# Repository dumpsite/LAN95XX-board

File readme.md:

SMSC LAN95XX adapter board
==========================

This board serves as a carrier for the famous LAN95XX 
(LAN9512, LAN9513 or LAN9514) USB to fast Ethernet controller.

All the (high) frequency-, power- and decoupling stuff is done
on the board, while the most interesting pins are routed to the
outside edges. There the pitch is the usual 2.54mm (0.1") and
easily accessible for any further projects.

The board features an onboard eeprom (type "93C56 or 93C66") in cheap
SO8 package and implements a 25 MHz 5032 SMD crystal circuit.
(For cheaper HC49* versions there was no space...)
The smallest component is 0603, but most of them are replaceable with some 0805...

All is done (and works!) with two active design layers only!
A theoretical third layer is "emulated" by connecting some edge-pins together.
So it needs not be produced with the PCB itself...
The traces are scaled a bit thinner to compensate spreading during design transfer
to copper. All package footprints are using longer pin pads.
The primary IC (LAN95XX) QFN package footprint is extended by an 3.2mm inner
bonding hole, allowing backside soldering and solder bridging the two layers.

All this allows fully DIY capability and "etching at home".
VIAs can be drilled using 0.2mm or 0.3mm drill.
Side-to-side bonding can be done using stripped AWG30 wire wrapping wire.

The minimal essential size is "33mm x 33mm" using castellations or
"36mm x 36mm" using full pin headers.
Including the whole PCB area having the board nicely centered, its
dimensions are "50mm x 50mm" .

All the content is open and freely usable in non commercial applications.
It would be very kind to mention me in your projects and ask me first if you plan commercial use...

by Stephan Baerwolf (stephan@matrixstorm.com), Schwansee 2016

(who is not bearing any responsibility or guarantee of any kind for his projects)

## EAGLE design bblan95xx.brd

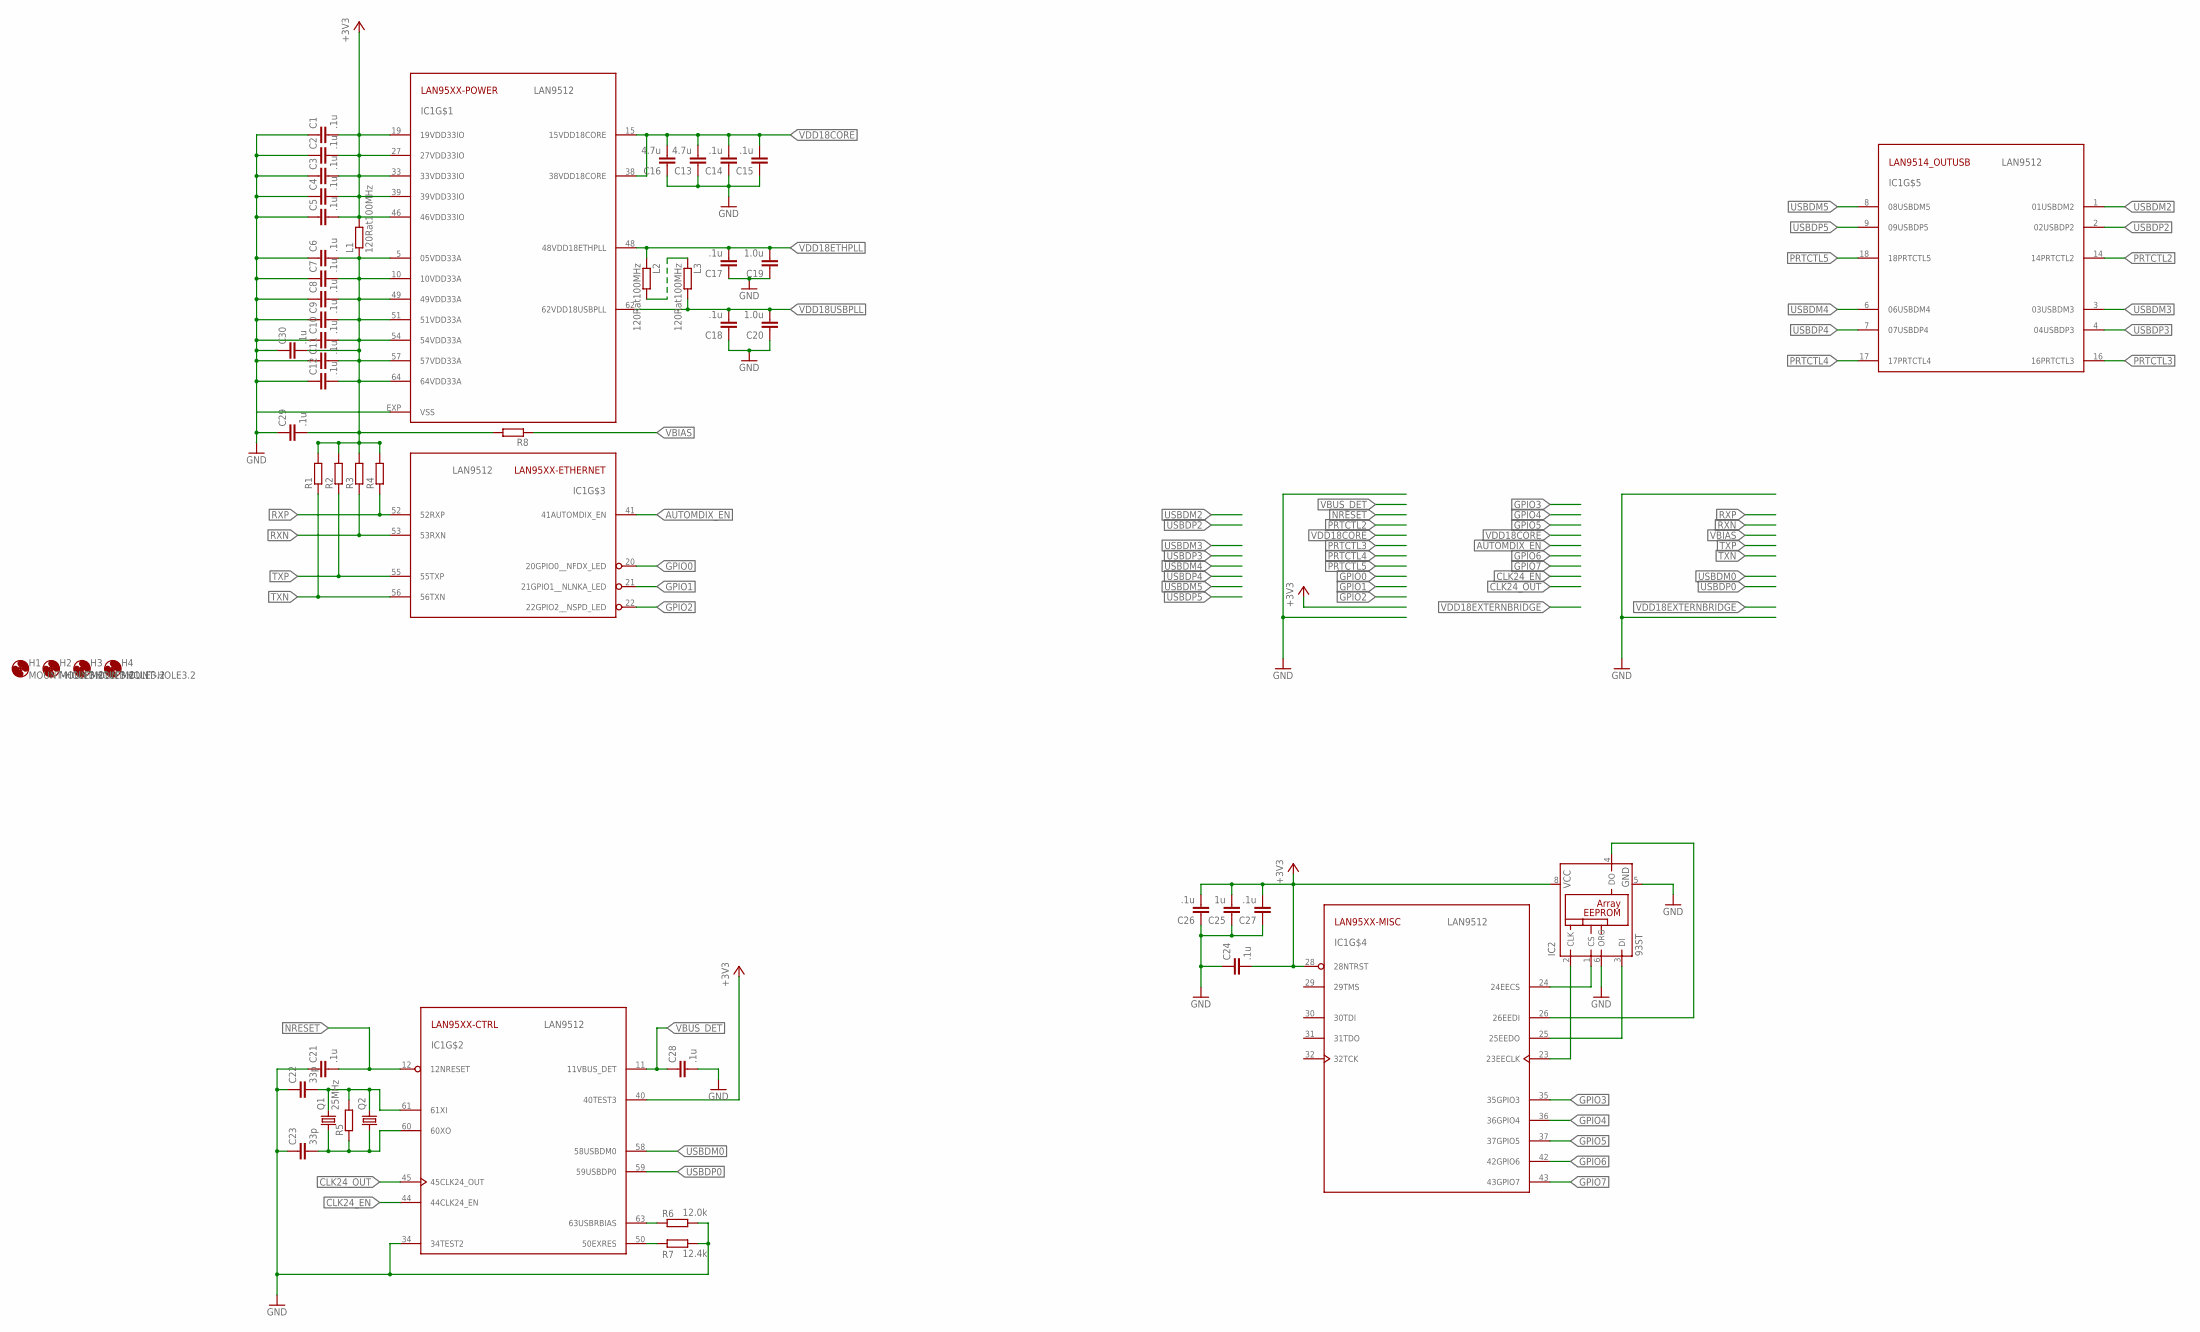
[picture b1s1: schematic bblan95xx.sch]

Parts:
C1, C2, C3, C4, C5, C6, C7, C8, C12, C26, C27: .1u; C0805K
C9, C10, C11, C14, C15, C17, C18, C21, C24, C28, C29, C30: .1u; C0603K
C13, C16: 4.7u; C0805K
C19, C20: 1.0u; C0805K
C22, C23: 33p; C0603K
C25: 1u; C0805K
H1, H2, H3, H4: MOUNT-HOLE3.2; 3,2
IC1: LAN9512; QFN64-9X9-EXTRALONG
IC2: 93ST; SO-08
L1, L2, L3: 120Rat100MHz; R0805
Q1: 25MHz; CRYSTAL-SMD-5X3
Q2: CRYSTALHC49S; HC49/S
R1, R2, R3, R4, R5: R-EU_R0603; R0603
R6: 12.0k; R0603
R7: 12.4k; R0603
R8: R-EU_R0402; R0402

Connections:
+3V3: C1.2, C2.2, C3.2, C4.2, C5.2, C24.2, C25.2, C26.2, C27.2, IC1.19 (19VDD33IO), IC1.27 (27VDD33IO), IC1.28 (28NTRST), IC1.33 (33VDD33IO), IC1.39 (39VDD33IO), IC1.40 (40TEST3), IC1.46 (46VDD33IO), IC2.8 (VCC), L1.2
AUTOMDIX_EN: IC1.41 (41AUTOMDIX_EN)
CLK24_EN: IC1.44 (44CLK24_EN)
CLK24_OUT: IC1.45 (45CLK24_OUT)
EECLK: IC1.23 (23EECLK), IC2.2 (CLK)
EECS: IC1.24 (24EECS), IC2.1 (CS)
EEDI: IC1.26 (26EEDI), IC2.4 (DO)
EEDO: IC1.25 (25EEDO), IC2.3 (DI)
GND: C1.1, C2.1, C3.1, C4.1, C5.1, C6.1, C7.1, C8.1, C9.1, C10.1, C11.1, C12.1, C13.1, C14.1, C15.1, C16.1, C17.1, C18.1, C19.1, C20.1, C21.1, C22.1, C23.1, C24.1, C25.1, C26.1, C27.1, C28.2, C29.1, C30.1, IC1.34 (34TEST2), IC1.EXP (VSS), IC2.5 (GND), IC2.6 (ORG), R6.2, R7.2
GPIO0: IC1.20 (20GPIO0__NFDX_LED)
GPIO1: IC1.21 (21GPIO1__NLNKA_LED)
GPIO2: IC1.22 (22GPIO2__NSPD_LED)
GPIO3: IC1.35 (35GPIO3)
GPIO4: IC1.36 (36GPIO4)
GPIO5: IC1.37 (37GPIO5)
GPIO6: IC1.42 (42GPIO6)
GPIO7: IC1.43 (43GPIO7)
unnamed: IC1.63 (63USBRBIAS), R6.1
unnamed: IC1.50 (50EXRES), R7.1
NRESET: C21.2, IC1.12 (12NRESET)
PRTCTL2: IC1.14 (14PRTCTL2)
PRTCTL3: IC1.16 (16PRTCTL3)
PRTCTL4: IC1.17 (17PRTCTL4)
PRTCTL5: IC1.18 (18PRTCTL5)
RXN: IC1.53 (53RXN), R3.1
RXP: IC1.52 (52RXP), R4.1
TXN: IC1.56 (56TXN), R1.1
TXP: IC1.55 (55TXP), R2.1
USBDM0: IC1.58 (58USBDM0)
USBDM2: IC1.1 (01USBDM2)
USBDM3: IC1.3 (03USBDM3)
USBDM4: IC1.6 (06USBDM4)
USBDM5: IC1.8 (08USBDM5)
USBDP0: IC1.59 (59USBDP0)
USBDP2: IC1.2 (02USBDP2)
USBDP3: IC1.4 (04USBDP3)
USBDP4: IC1.7 (07USBDP4)
USBDP5: IC1.9 (09USBDP5)
VBIAS: R8.1
VBUS_DET: C28.1, IC1.11 (11VBUS_DET)
VDD18CORE: C13.2, C14.2, C15.2, C16.2, IC1.15 (15VDD18CORE), IC1.38 (38VDD18CORE)
VDD18ETHPLL: C17.2, C19.2, IC1.48 (48VDD18ETHPLL), L2.1
VDD18EXTERNBRIDGE: L2.2, L3.1
VDD18USBPLL: C18.2, C20.2, IC1.62 (62VDD18USBPLL), L3.2
VDD33A: C6.2, C7.2, C8.2, C9.2, C10.2, C11.2, C12.2, C29.2, C30.2, IC1.5 (05VDD33A), IC1.10 (10VDD33A), IC1.49 (49VDD33A), IC1.51 (51VDD33A), IC1.54 (54VDD33A), IC1.57 (57VDD33A), IC1.64 (64VDD33A), L1.1, R1.2, R2.2, R3.2, R4.2, R8.2
XI: C22.2, IC1.61 (61XI), Q1.3 (2), Q2.2, R5.2
XO: C23.2, IC1.60 (60XO), Q1.1, Q2.1, R5.1

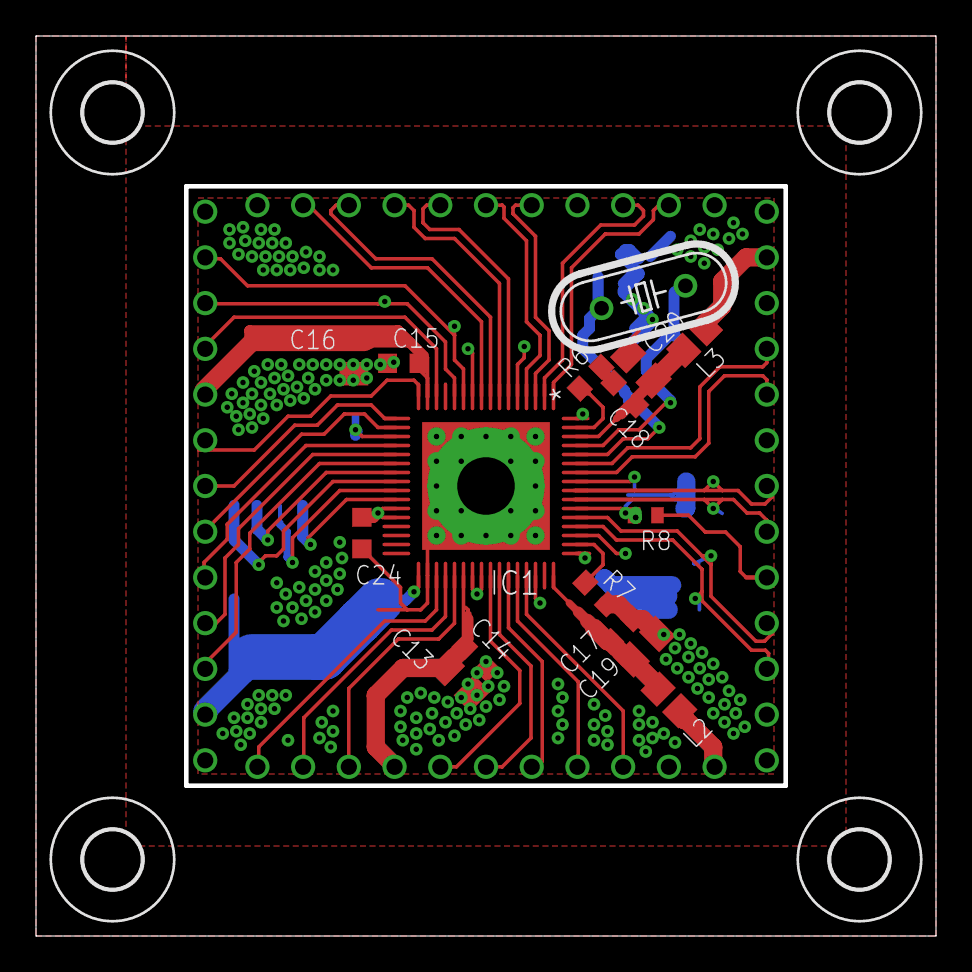
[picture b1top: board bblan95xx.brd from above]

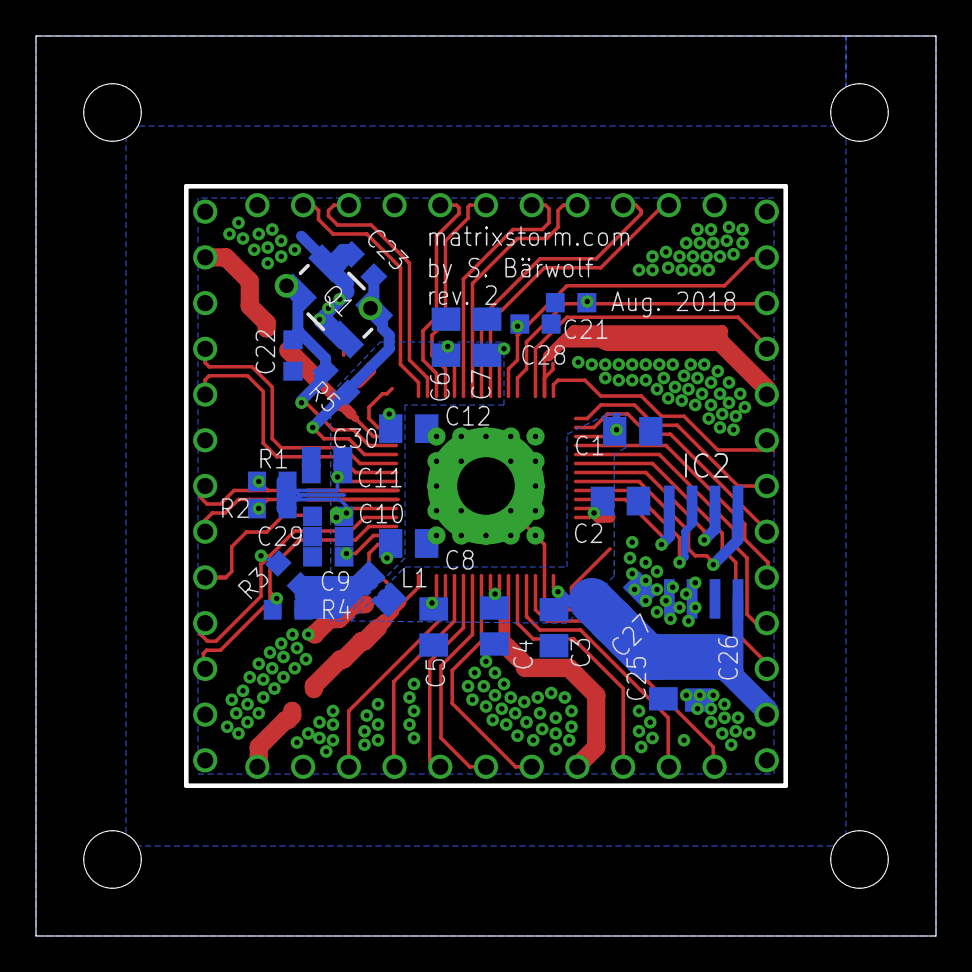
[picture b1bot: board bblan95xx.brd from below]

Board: 3 copper layers, 49.7 x 49.7 mm, 49 parts (29 on the bottom side), 21 nets.

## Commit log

2016-10-16 initial repository fill
2016-10-16 starting LAN95xx base board design
2016-10-16 shrink primary polygons to final adapter size
2016-10-16 add extra 0603 cap and make 0603 to 0805 where possible
2016-10-16 add extra analog capacitor and route VDD33A to free PIN
2016-10-16 accept all warnings and errors since board is fine
2016-10-16 add more vias to connect GND planes
2016-10-16 add also thermal vias to main IC
2016-10-16 mirror pinjumper headers in bottom direction
2016-10-16 reroute USB down-port two and crystal cap
2016-10-16 add pseudo c-tool for generating eeprom image during compile
    This patch allows the creation of eeprom-images for the LAN95XX board.
    The current default is for LAN9512 and disables all downstream USB ports.
    So it is for designs just using the ethernet functionality.
    To program data into the eeprom you can use for example ethtool:
    "cat eeprom.bin | ethtool -E ethX magic 0x9500 offset 0x0"
    To change things simply edit the lan95xx_eeprom_configurator.c and
2016-10-16 Fill middle layer "PCBnoRoute" with groundplane
    In case somebody cares to produce a multilayer PCB instead externally connecting
    the Vcore pins, present a nicer middle layer.
2016-10-19 mirror pinjumper headers try two
    Mirror and rotate JPUSBDOWN and JPMISC
2016-10-19 add some edge polygons on all copper layers
2016-10-23 spruce up name layer on top
2016-10-23 spruce up name layer on bottom
2016-10-23 finalize gerberizable version 1.2.0
    For silkscreen it is recommended to use additional to "20 Dimension":
    * "51 tDocu" , "25 tNames" and "21 tPlace"
    or for bottom:
    * "52 bDocu" , "26 bNames" and "22 bPlace"
2016-10-24 add an example tool to access the lan95xx controller
    This commit implements a small (quick and dirty) demonstration,
    how to access the controller via userspace USB (libusb) to
    do some stuff.
    In this case access the chip ID or statistical data.
    Both can be used to check the quality of the final solder job.
    (Or the ordered chip by that matter...)
2016-10-24 add udev-rule to use lan95xx tool as non-root user on linux
2016-11-27 fix: some minor bugs in eeprom around usb-hub configuration
    First make USB-HUB selfpower feature depending on "LAN951X_SELFPOWERED".
    The eeprom header, as also the USB descriptors already are using it.
    (Before this the USB-Hub always indicated to be self-powered...)
    Second: Do not disable overcurrent sensing, since this will violate USB standard when self powering.
    Third: Do not register as (not removable) compound device.
2016-11-28 add more details to help usage of lan95xxtool
2016-11-28 extend lan95xxtool for reading and writing registers
    So for example the call:
    ./lan95xxtool chipid
    equals then
    ./lan95xxtool rr:0
    Following will read the BULK IN DELAY REGISTER (BULK_IN_DLY):
    ./lan95xxtool rr:6c
2016-11-28 fix last line of readme.md by adding crlf
2016-12-04 add eagle library of board footprint for ease of use in further projects
2016-12-10 extend eagle library of board with minimal footprint
2017-03-25 extend lan95xxtool for reading and writing the PHY
2017-03-25 extend lan95xxtool for dumping the eeprom
2017-03-25 add bblan95xx pinout artwork
    For correct display, please nake shure you have "Monaco_Linux.ttf" installed.
2017-03-27 fix wrong include for windows cross compiles in lantool
2019-11-17 mutilate schematic (remove pinheaders)...
    ...to finalize rev2 panelizeable board.
2019-11-17 improve pcb yield by optimizing PCB to revision 2
    However the pinheaders remain either for castellations but more
    because they are in the original schematic. (While the big
    vias as holes instead are not)
    When creating a panel the pinheaders can be removed.
    But beware of the lables not to go away, too...
2019-11-17 ran panelize.ulp to generate name layers 125+126
    This is the preparation to remove the pinheaders, but
    not their name in the silkscreen.

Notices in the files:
parts and their libraries:
SparkFun: Licensing: CC v3.0 Share-Alike You are welcome to use this library for commercial purposes.
SparkFun-Aesthetics: Licensing: Creative Commons ShareAlike 4.0 International - https://creativecommons.org/licenses/by-sa/4.0
